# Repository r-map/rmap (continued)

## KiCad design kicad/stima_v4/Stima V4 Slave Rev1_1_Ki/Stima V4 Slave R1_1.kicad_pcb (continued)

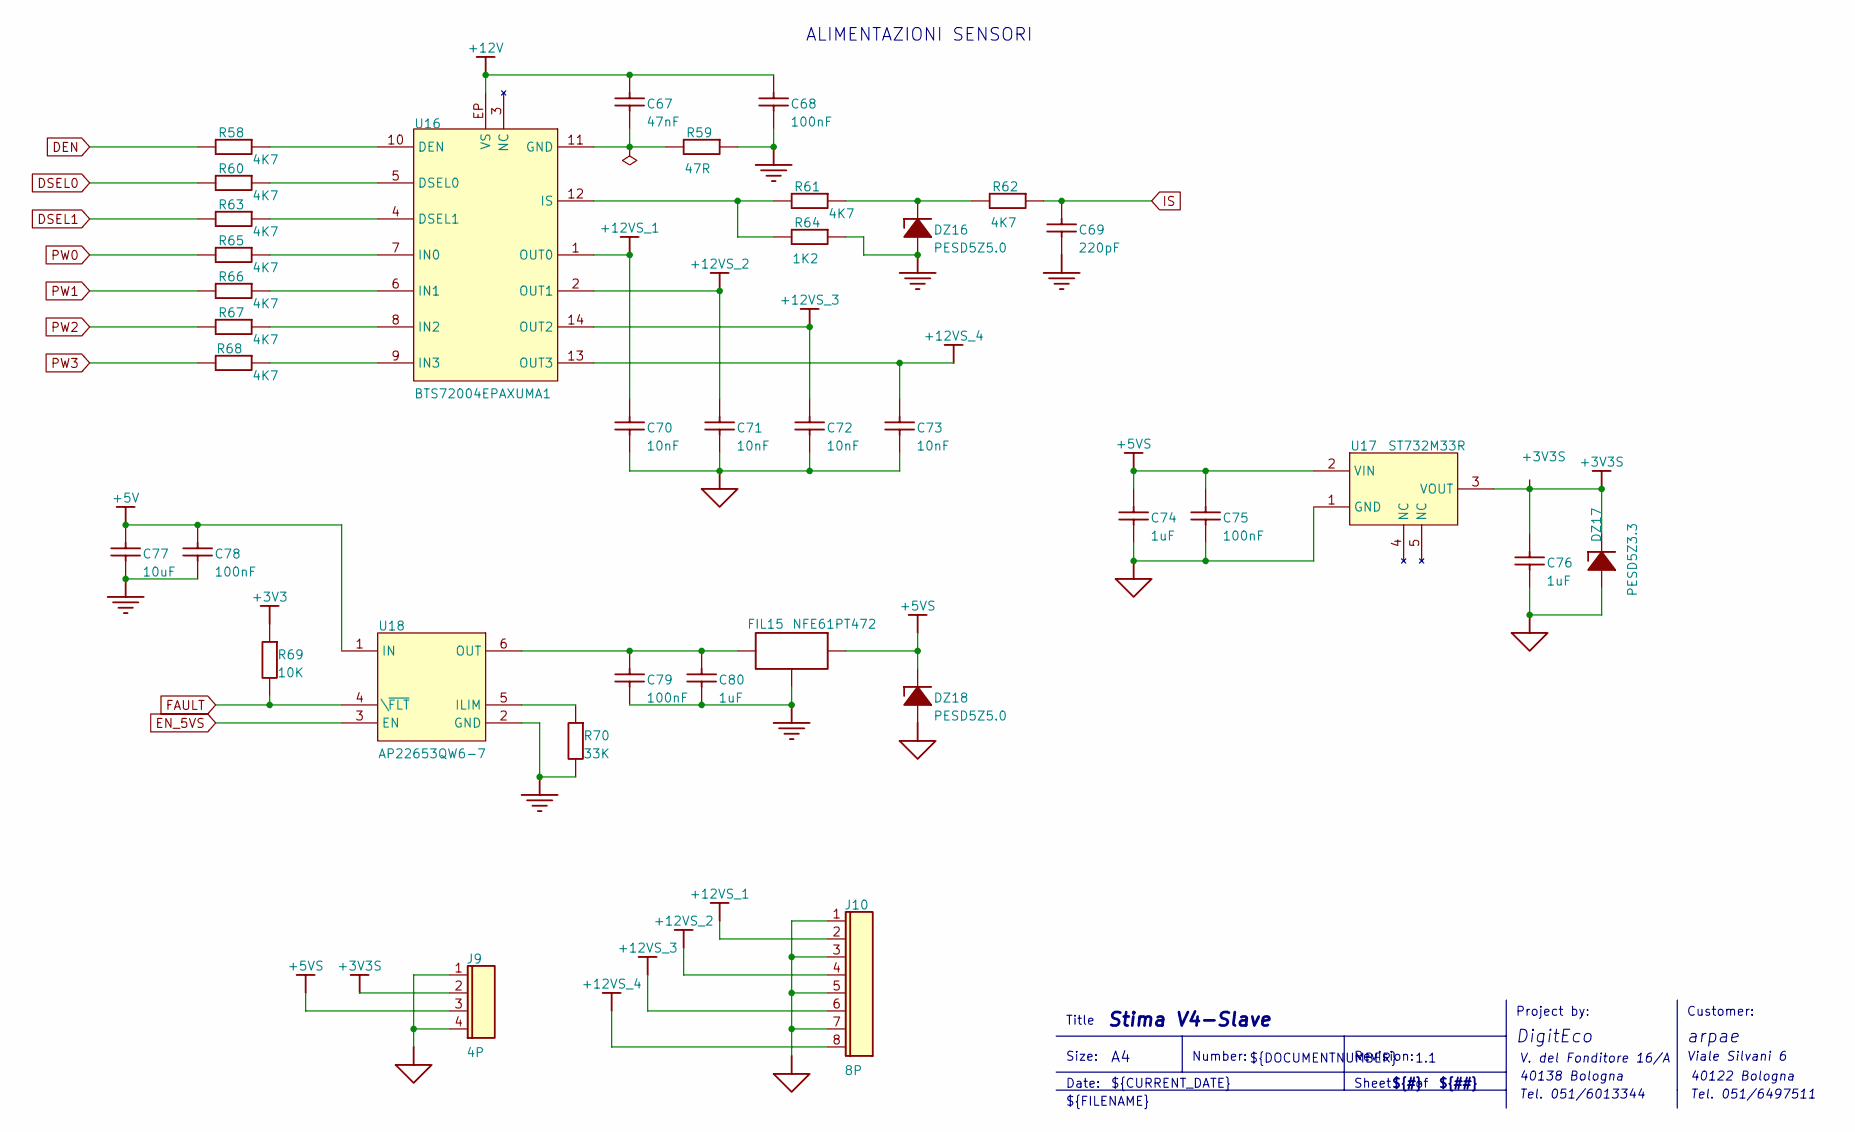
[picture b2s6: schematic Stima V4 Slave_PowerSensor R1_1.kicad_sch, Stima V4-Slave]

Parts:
+3V3S: TestPoint; TP
C67: 47nF; 0603; VOLTAGE 50V
C68, C75, C78, C79: 100nF; 0603; VOLTAGE 50V
C69: 220pF; 0603; VOLTAGE 50V
C70, C71, C72, C73: 10nF; 0603; VOLTAGE 50V
C74, C76, C80: 1uF; 0603; VOLTAGE 20V
C77: 10uF; 0603; VOLTAGE 20V
DZ16, DZ18: PESD5Z5.0; SOD 523(SC-79)
DZ17: PESD5Z3.3; SOD 523(SC-79)
FIL15: NFE61PT472; NFE61PT-2606
J9: 4P; CONN_4P-P381
J10: 8P; CONN_8P-P381
R58, R60, R61, R62, R63, R65, R66, R67, R68: 4K7; 0603
R59: 47R; 0603
R64: 1K2; 0603
R69: 10K; 0603
R70: 33K; 0603
U16: BTS72004EPAXUMA1; TSDSO-14
U17: ST732M33R; SOT23_5
U18: AP22653QW6-7; SOT26

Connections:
+3V3: R69.1; also elsewhere on the board
+3V3S: C76.1, DZ17.1 (K), J9.2, U17.3 (VOUT); also elsewhere on the board
+5V: C77.1, C78.1, U18.1 (IN); also elsewhere on the board
+5VS: C74.1, C75.1, DZ18.1 (K), FIL15.2 (O), J9.3, U17.2 (VIN); also elsewhere on the board
+12V: C67.1, C68.1, U16.EP (VS); also elsewhere on the board
+12VS_1: C70.1, J10.2, U16.1 (OUT0)
+12VS_2: C71.1, J10.4, U16.2 (OUT1)
+12VS_3: C72.1, J10.6, U16.14 (OUT2)
+12VS_4: C73.1, J10.8, U16.13 (OUT3); also elsewhere on the board
DEN: R58.1; also elsewhere on the board
DSEL0: R60.1; also elsewhere on the board
DSEL1: R63.1; also elsewhere on the board
EGND: C70.2, C71.2, C72.2, C73.2, C74.2, C75.2, C76.2, DZ17.2 (A), DZ18.2 (A), J9.1, J9.4, J10.1, J10.3, J10.5, J10.7, U17.1 (GND); also elsewhere on the board
EN_5VS: U18.3 (EN); also elsewhere on the board
FAULT: R69.2, U18.4 (\~FLT); also elsewhere on the board
GND: C68.2, C69.2, C77.2, C78.2, C79.2, C80.2, DZ16.2 (A), FIL15.3, R59.2, R64.2, R70.2, U18.2 (GND); also elsewhere on the board
IS: C69.1, R62.2; also elsewhere on the board
unnamed: DZ16.1 (K), R61.2, R62.1
unnamed: C79.1, C80.1, FIL15.1 (I), U18.6 (OUT)
unnamed: R58.2, U16.10 (DEN)
unnamed: R60.2, U16.5 (DSEL0)
unnamed: R63.2, U16.4 (DSEL1)
unnamed: C67.2, R59.1, U16.11 (GND)
unnamed: R65.2, U16.7 (IN0)
unnamed: R66.2, U16.6 (IN1)
unnamed: R67.2, U16.8 (IN2)
unnamed: R68.2, U16.9 (IN3)
unnamed: R61.1, R64.1, U16.12 (IS)
unnamed: R70.1, U18.5 (ILIM)
PW0: R65.1; also elsewhere on the board
PW1: R66.1; also elsewhere on the board
PW2: R67.1; also elsewhere on the board
PW3: R68.1; also elsewhere on the board

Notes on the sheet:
V. del Fonditore 16/A
Tel. 051/6013344
Title
Viale Silvani 6
ALIMENTAZIONI SENSORI
Size:
DigitEco
${##}
Tel. 051/6497511
arpae
Date:
${TITLE}
${#}
Project by:
Number:
${DOCUMENTNUMBER}
40122 Bologna
40138 Bologna
Revision:
Sheet
1.1
${FILENAME}
${CURRENT_DATE}
Customer:

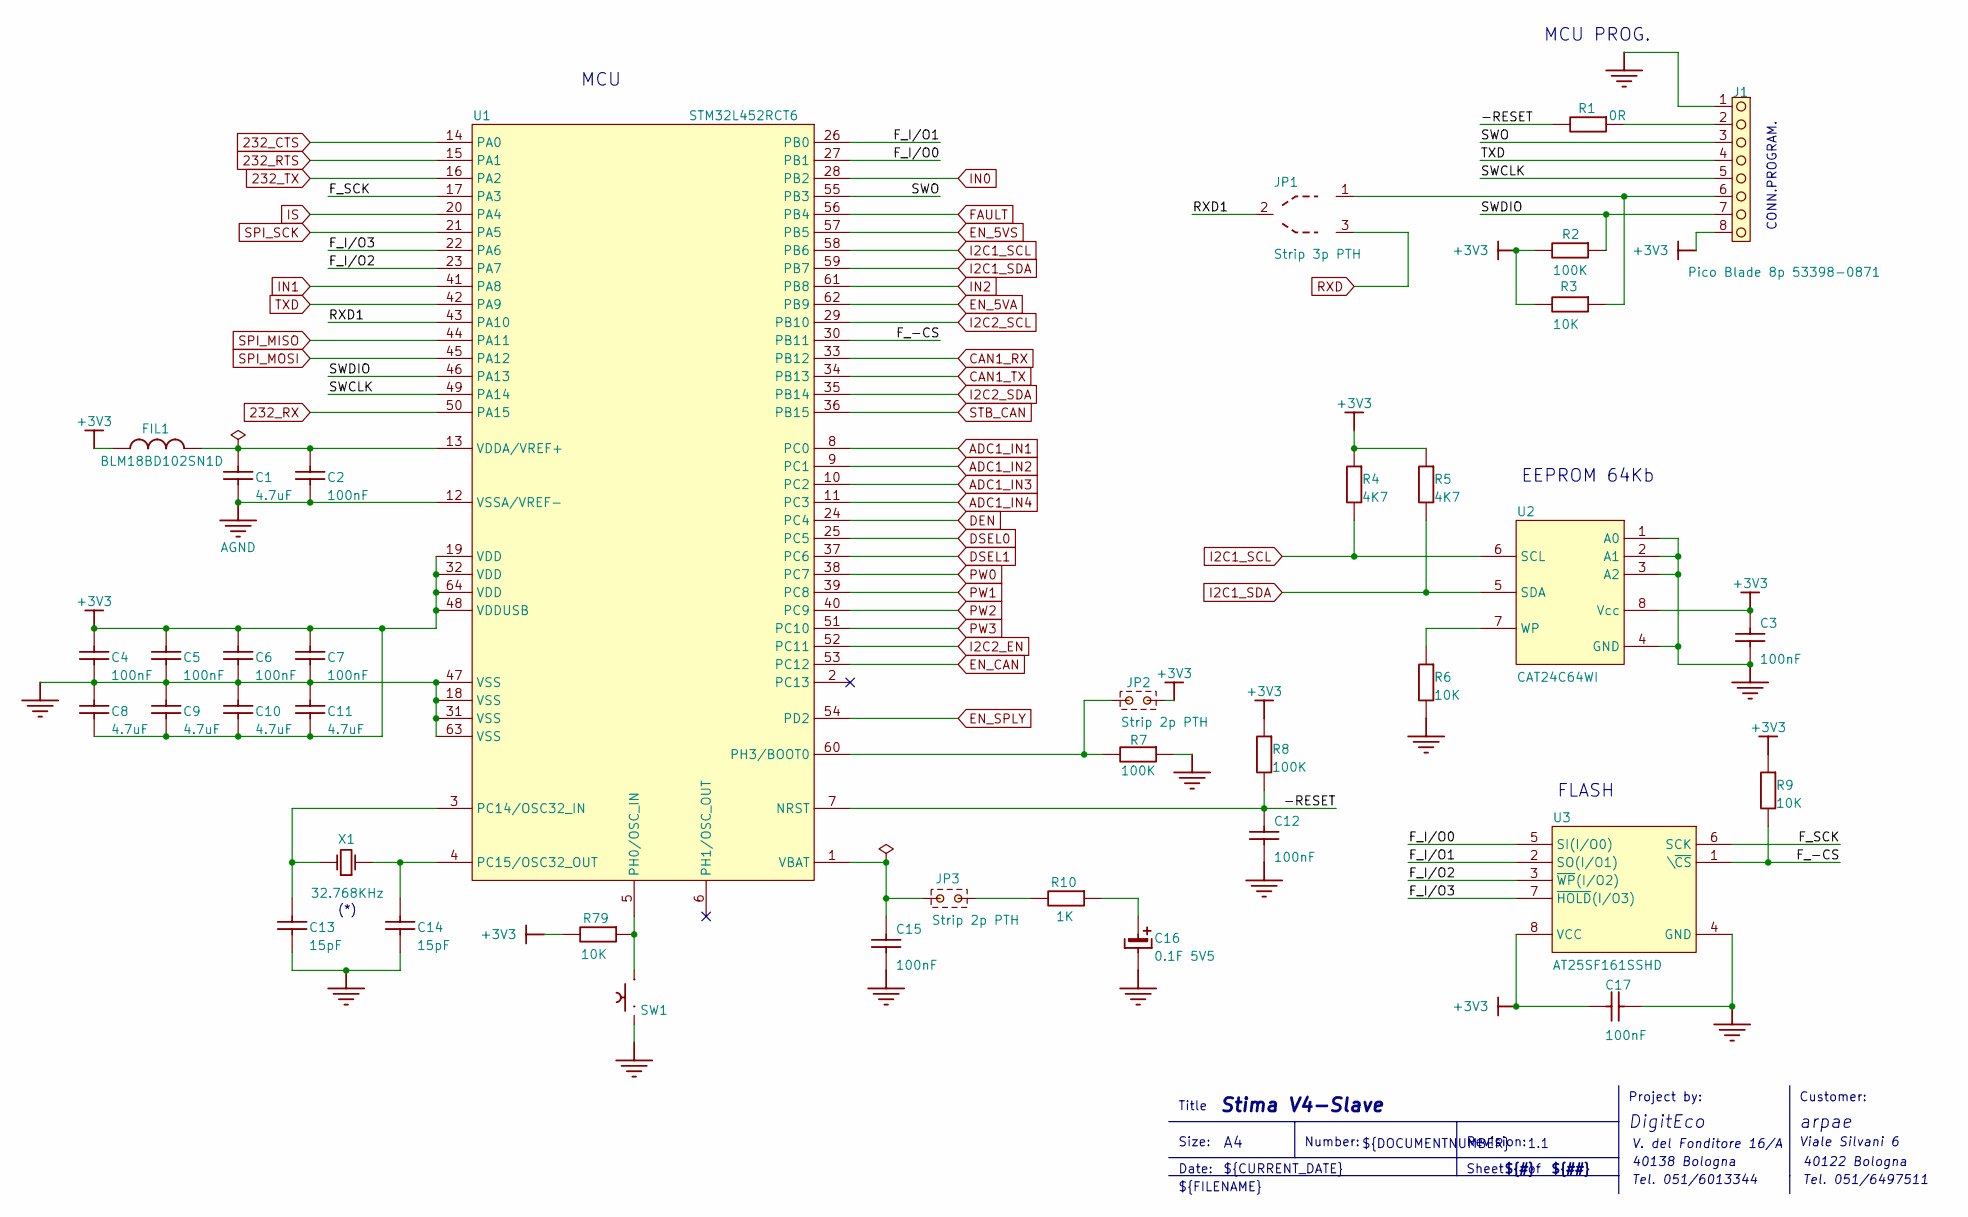
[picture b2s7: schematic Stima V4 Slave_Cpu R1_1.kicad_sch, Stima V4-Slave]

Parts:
C1, C8, C9, C10, C11: 4.7uF; 0603; VOLTAGE 16V
C2, C4, C5, C6, C7, C17: 100nF; 0603; VOLTAGE 50V
C3, C12, C15: 100nF; 0805; VOLTAGE 50V
C13, C14: 15pF; 0603; VOLTAGE 50V
C16: 0.1F 5V5; 10X8-10_5; VOLTAGE 5V5
FIL1: BLM18BD102SN1D; 0603
J1: Pico Blade 8p 53398-0871; MOLEX8P1_25SMD
JP1: Strip 3p PTH; STRIP3PP254
JP2, JP3: Strip 2p PTH; STRIP2P
R1: 0R; 0603
R2, R7, R8: 100K; 0603
R3, R6, R9, R79: 10K; 0603
R4, R5: 4K7; 0603
R10: 1K; 0603
SW1: B3F xx; TASTO SMD 6X6
U1: STM32L452RCT6; LQFP64
U2: CAT24C64WI; SO8
U3: AT25SF161SSHD; SO8
X1: 32.768KHz; CRYST_ECS

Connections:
232_CTS: U1.14 (PA0); also elsewhere on the board
232_RTS: U1.15 (PA1); also elsewhere on the board
232_RX: U1.50 (PA15); also elsewhere on the board
232_TX: U1.16 (PA2); also elsewhere on the board
+3V3: C3.1, C4.1, C5.1, C6.1, C7.1, C8.2, C9.2, C10.2, C11.2, C17.1, FIL1.1, J1.8, JP2.2, R2.1, R3.1, R4.2, R5.2, R8.2, R9.2, R79.2, U1.19 (VDD), U1.32 (VDD), U1.48 (VDDUSB), U1.64 (VDD), U2.8 (Vcc), U3.8 (VCC); also elsewhere on the board
/Stima V4 Slave_Cpu R1_1/-RESET: C12.1, R1.1, R8.1, U1.7 (NRST)
/Stima V4 Slave_Cpu R1_1/F_-CS: R9.1, U1.30 (PB11), U3.1 (\~CS)
/Stima V4 Slave_Cpu R1_1/F_I/O0: U1.27 (PB1), U3.5 (SI(I/O0))
/Stima V4 Slave_Cpu R1_1/F_I/O1: U1.26 (PB0), U3.2 (SO(I/O1))
/Stima V4 Slave_Cpu R1_1/F_I/O2: U1.23 (PA7), U3.3 (~WP(I/O2))
/Stima V4 Slave_Cpu R1_1/F_I/O3: U1.22 (PA6), U3.7 (~HOLD(I/O3))
/Stima V4 Slave_Cpu R1_1/F_SCK: U1.17 (PA3), U3.6 (SCK)
/Stima V4 Slave_Cpu R1_1/RXD1: JP1.2, U1.43 (PA10)
/Stima V4 Slave_Cpu R1_1/SWCLK: J1.5, U1.49 (PA14)
/Stima V4 Slave_Cpu R1_1/SWDIO: J1.7, R2.2, U1.46 (PA13)
/Stima V4 Slave_Cpu R1_1/SWO: J1.3, U1.55 (PB3)
ADC1_IN1: U1.8 (PC0); also elsewhere on the board
ADC1_IN2: U1.9 (PC1); also elsewhere on the board
ADC1_IN3: U1.10 (PC2); also elsewhere on the board
ADC1_IN4: U1.11 (PC3); also elsewhere on the board
AGND: C1.2, C2.2, U1.12 (VSSA/VREF-); also elsewhere on the board
CAN1_RX: U1.33 (PB12); also elsewhere on the board
CAN1_TX: U1.34 (PB13); also elsewhere on the board
DEN: U1.24 (PC4); also elsewhere on the board
DSEL0: U1.25 (PC5); also elsewhere on the board
DSEL1: U1.37 (PC6); also elsewhere on the board
EN_5VA: U1.62 (PB9); also elsewhere on the board
EN_5VS: U1.57 (PB5); also elsewhere on the board
EN_CAN: U1.53 (PC12); also elsewhere on the board
EN_SPLY: U1.54 (PD2); also elsewhere on the board
FAULT: U1.56 (PB4); also elsewhere on the board
GND: C3.2, C4.2, C5.2, C6.2, C7.2, C8.1, C9.1, C10.1, C11.1, C12.2, C13.2, C14.2, C15.2, C16.2, C17.2, J1.1, R6.1, R7.2, SW1.1, SW1.2, U1.18 (VSS), U1.31 (VSS), U1.47 (VSS), U1.63 (VSS), U2.1 (A0), U2.2 (A1), U2.3 (A2), U2.4 (GND), U3.4 (GND); also elsewhere on the board
I2C1_SCL: R4.1, U1.58 (PB6), U2.6 (SCL); also elsewhere on the board
I2C1_SDA: R5.1, U1.59 (PB7), U2.5 (SDA); also elsewhere on the board
I2C2_EN: U1.52 (PC11); also elsewhere on the board
I2C2_SCL: U1.29 (PB10); also elsewhere on the board
I2C2_SDA: U1.35 (PB14); also elsewhere on the board
IN0: U1.28 (PB2); also elsewhere on the board
IN1: U1.41 (PA8); also elsewhere on the board
IN2: U1.61 (PB8); also elsewhere on the board
IS: U1.20 (PA4); also elsewhere on the board
unnamed: C16.1, R10.2
unnamed: J1.2, R1.2
unnamed: J1.6, JP1.1, R3.2
unnamed: JP3.2, R10.1
unnamed: C13.1, U1.3 (PC14/OSC32_IN), X1.2 (OSC2)
unnamed: C14.1, U1.4 (PC15/OSC32_OUT), X1.1 (OSC1)
unnamed: R79.1, SW1.3, SW1.4, U1.5 (PH0/OSC_IN)
unnamed: JP2.1, R7.1, U1.60 (PH3/BOOT0)
unnamed: C15.1, JP3.1, U1.1 (VBAT)
unnamed: C1.1, C2.1, FIL1.2, U1.13 (VDDA/VREF+)
unnamed: R6.2, U2.7 (WP)
PW0: U1.38 (PC7); also elsewhere on the board
PW1: U1.39 (PC8); also elsewhere on the board
PW2: U1.40 (PC9); also elsewhere on the board
PW3: U1.51 (PC10); also elsewhere on the board
RXD: JP1.3; also elsewhere on the board
SPI_MISO: U1.44 (PA11); also elsewhere on the board
SPI_MOSI: U1.45 (PA12); also elsewhere on the board
SPI_SCK: U1.21 (PA5); also elsewhere on the board
STB_CAN: U1.36 (PB15); also elsewhere on the board
TXD: J1.4, U1.42 (PA9); also elsewhere on the board

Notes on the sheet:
MCU
(*)
${FILENAME}
1.1
${##}
Viale Silvani 6
Project by:
${DOCUMENTNUMBER}
Title
EEPROM 64Kb
Tel. 051/6013344
${CURRENT_DATE}
Date:
${TITLE}
Number:
40122 Bologna
arpae
MCU PROG.
Customer:
Revision:
DigitEco
Sheet
V. del Fonditore 16/A
Size:
Tel. 051/6497511
40138 Bologna
${#}
CONN.PROGRAM.
FLASH

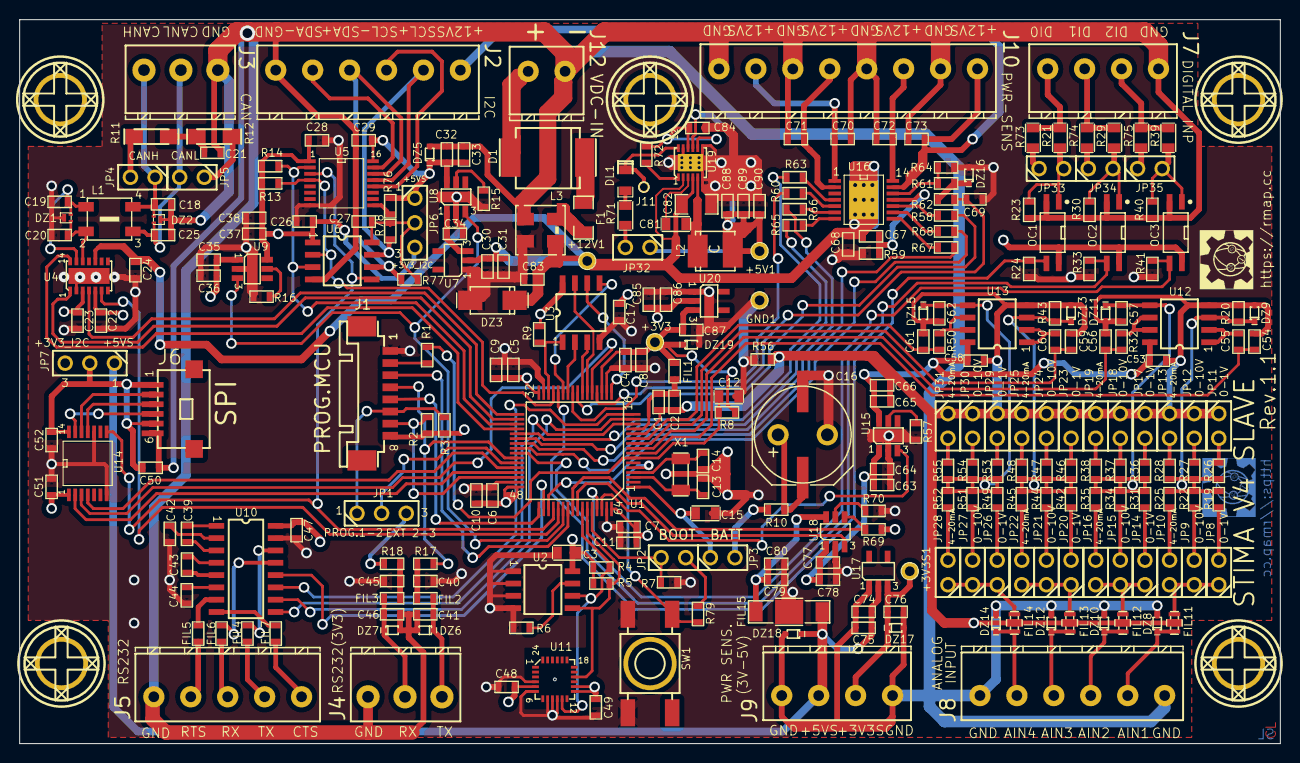
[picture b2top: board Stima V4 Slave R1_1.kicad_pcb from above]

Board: 4 copper layers, 130.0 x 74.7 mm, 288 parts (1 on the bottom side), 184 nets.

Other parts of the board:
+3V3S1: TestPoint; TP

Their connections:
+3V3S: +3V3S1.1; also elsewhere on the board

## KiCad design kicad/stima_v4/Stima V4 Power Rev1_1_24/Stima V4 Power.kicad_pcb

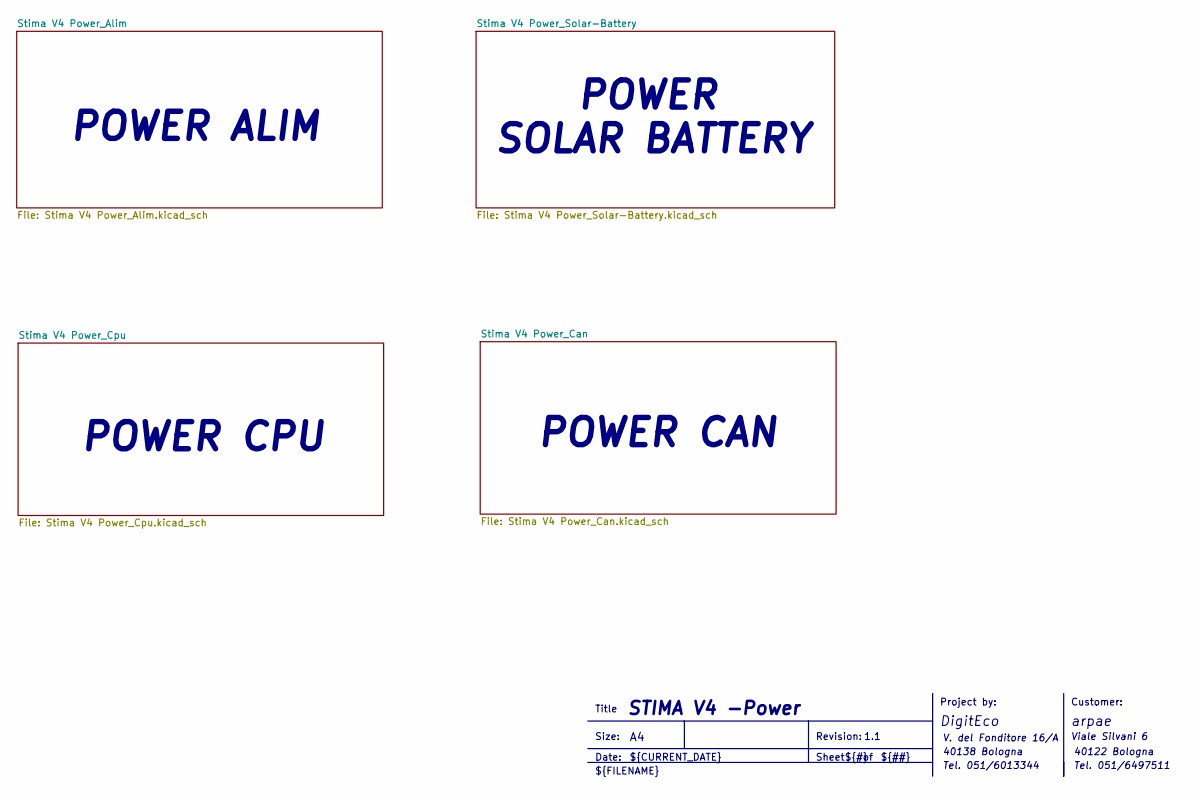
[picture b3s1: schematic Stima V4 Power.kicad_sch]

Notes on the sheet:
Tel. 051/6013344
${#}
arpae
POWER ALIM
Revision:
40138 Bologna
${TITLE}
Size:
V. del Fonditore 16/A
${##}
Viale Silvani 6
${CURRENT_DATE}
Sheet
Tel. 051/6497511
Date:
POWER SOLAR BATTERY
Customer:
40122 Bologna
Project by:
${FILENAME}
STIMA V4 -Power
DigitEco
Title
1.1
POWER CAN
POWER CPU

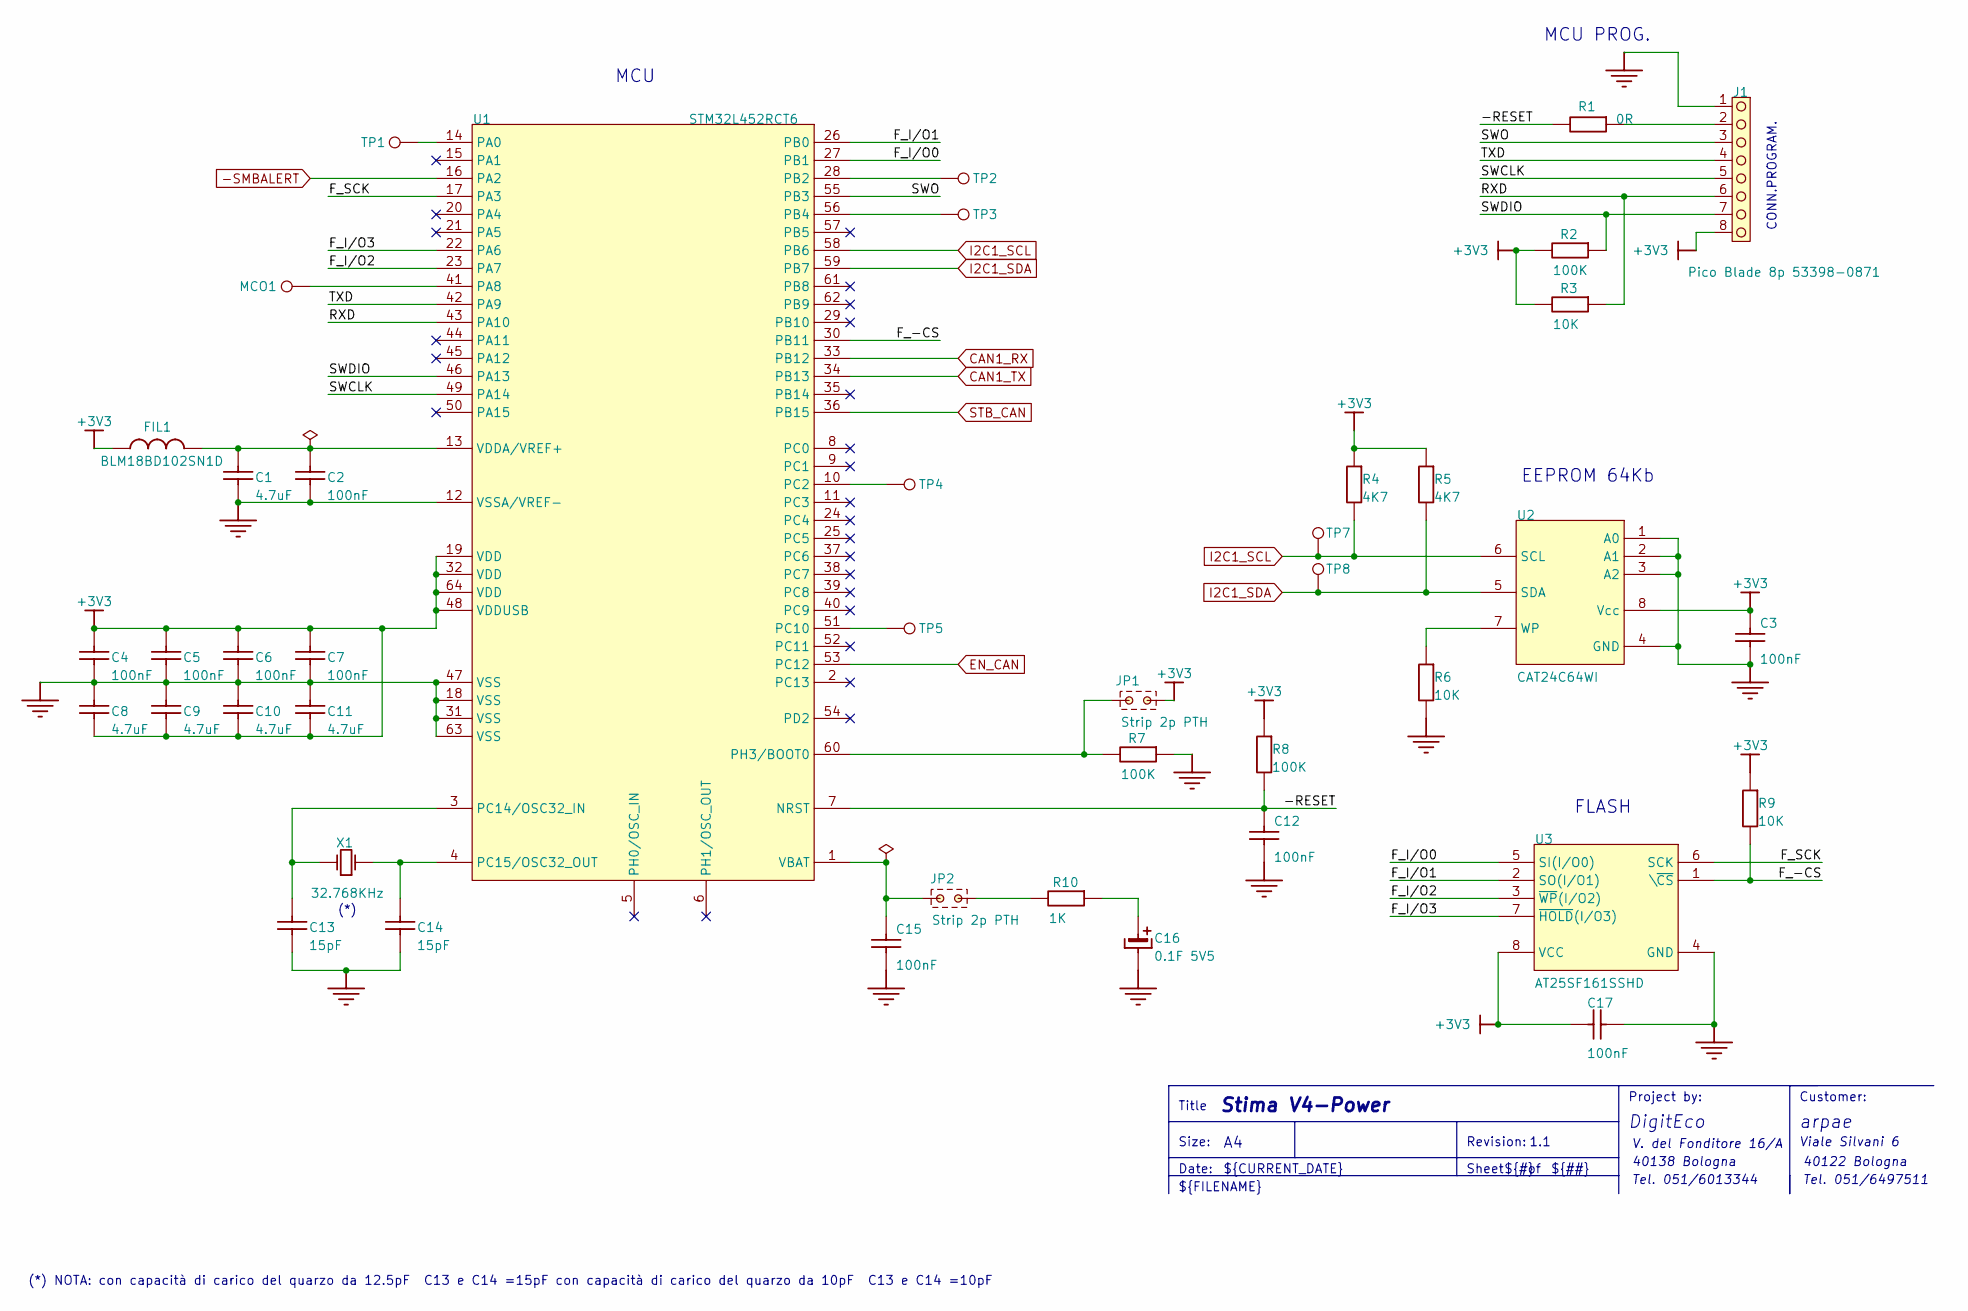
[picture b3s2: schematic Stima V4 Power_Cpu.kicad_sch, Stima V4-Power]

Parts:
C1, C8, C9, C10, C11: 4.7uF; 0603; VOLTAGE 16V
C2, C3, C4, C5, C6, C7, C12, C15, C17: 100nF; 0603; VOLTAGE 50V
C13, C14: 15pF; 0603; VOLTAGE 50V
C16: 0.1F 5V5; CapELSUPERCAP-3D FT0H104ZF; VOLTAGE 5V5
FIL1: BLM18BD102SN1D; 0603
J1: Pico Blade 8p 53398-0871; MOLEX8P1_25SMD
JP1, JP2: Strip 2p PTH; STRIP2P
MCO1: TestPoint; TP
R1: 0R; 0603
R2, R7, R8: 100K; 0603
R3, R6, R9: 10K; 0603
R4, R5: 4K7; 0603
R10: 1K; 0603
TP1, TP2, TP3, TP4, TP5, TP7, TP8: TestPoint; TP
U1: STM32L452RCT6; LQFP64
U2: CAT24C64WI; SO8
U3: AT25SF161SSHD; SO8
X1: 32.768KHz; CRYST_ECS

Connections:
+3V3: C3.1, C4.1, C5.1, C6.1, C7.1, C8.2, C9.2, C10.2, C11.2, C17.1, FIL1.1, J1.8, R2.1, R3.1, R4.2, R5.2, R8.2, R9.2, U1.19 (VDD), U1.32 (VDD), U1.48 (VDDUSB), U1.64 (VDD), U2.8 (Vcc), U3.8 (VCC); also elsewhere on the board
-SMBALERT: U1.16 (PA2); also elsewhere on the board
/Stima V4 Power_Cpu/-RESET: C12.1, R1.1, R8.1, U1.7 (NRST)
/Stima V4 Power_Cpu/F_-CS: R9.1, U1.30 (PB11), U3.1 (\~CS)
/Stima V4 Power_Cpu/F_I/O0: U1.27 (PB1), U3.5 (SI(I/O0))
/Stima V4 Power_Cpu/F_I/O1: U1.26 (PB0), U3.2 (SO(I/O1))
/Stima V4 Power_Cpu/F_I/O2: U1.23 (PA7), U3.3 (~WP(I/O2))
/Stima V4 Power_Cpu/F_I/O3: U1.22 (PA6), U3.7 (~HOLD(I/O3))
/Stima V4 Power_Cpu/F_SCK: U1.17 (PA3), U3.6 (SCK)
/Stima V4 Power_Cpu/RXD: J1.6, R3.2, U1.43 (PA10)
/Stima V4 Power_Cpu/SWCLK: J1.5, U1.49 (PA14)
/Stima V4 Power_Cpu/SWDIO: J1.7, R2.2, U1.46 (PA13)
/Stima V4 Power_Cpu/SWO: J1.3, U1.55 (PB3)
/Stima V4 Power_Cpu/TXD: J1.4, U1.42 (PA9)
CAN1_RX: U1.33 (PB12); also elsewhere on the board
CAN1_TX: U1.34 (PB13); also elsewhere on the board
EN_CAN: U1.53 (PC12); also elsewhere on the board
GND: C1.2, C2.2, C3.2, C4.2, C5.2, C6.2, C7.2, C8.1, C9.1, C10.1, C11.1, C12.2, C13.2, C14.2, C15.2, C16.2, C17.2, J1.1, R6.1, R7.2, U1.12 (VSSA/VREF-), U1.18 (VSS), U1.31 (VSS), U1.47 (VSS), U1.63 (VSS), U2.1 (A0), U2.2 (A1), U2.3 (A2), U2.4 (GND), U3.4 (GND); also elsewhere on the board
I2C1_SCL: R4.1, TP7.1, U1.58 (PB6), U2.6 (SCL); also elsewhere on the board
I2C1_SDA: R5.1, TP8.1, U1.59 (PB7), U2.5 (SDA); also elsewhere on the board
unnamed 25: R10.1; also elsewhere on the board
unnamed: C16.1, R10.2
unnamed: J1.2, R1.2
unnamed: TP1.1, U1.14 (PA0)
unnamed: MCO1.1, U1.41 (PA8)
unnamed: TP2.1, U1.28 (PB2)
unnamed: TP3.1, U1.56 (PB4)
unnamed: TP4.1, U1.10 (PC2)
unnamed: TP5.1, U1.51 (PC10)
unnamed: C13.1, U1.3 (PC14/OSC32_IN), X1.2 (OSC2)
unnamed: C14.1, U1.4 (PC15/OSC32_OUT), X1.1 (OSC1)
unnamed 59: R7.1, U1.60 (PH3/BOOT0); also elsewhere on the board
unnamed 60: C15.1, U1.1 (VBAT); also elsewhere on the board
unnamed: C1.1, C2.1, FIL1.2, U1.13 (VDDA/VREF+)
unnamed: R6.2, U2.7 (WP)
STB_CAN: U1.36 (PB15); also elsewhere on the board

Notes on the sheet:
${FILENAME}
MCU PROG.
EEPROM 64Kb
${##}
V. del Fonditore 16/A
Title
Revision:
Date:
MCU
40122 Bologna
Sheet
Tel. 051/6497511
Tel. 051/6013344
arpae
DigitEco
${#}
Viale Silvani 6
Customer:
(*) NOTA: con capacità di carico del quarzo da 12.5pF C13 e C14 =15pF con capacità di carico del quarzo da 10pF C13 e C14 =10pF
(*)
${TITLE}
1.1
${CURRENT_DATE}
CONN.PROGRAM.
Project by:
Size:
40138 Bologna
FLASH

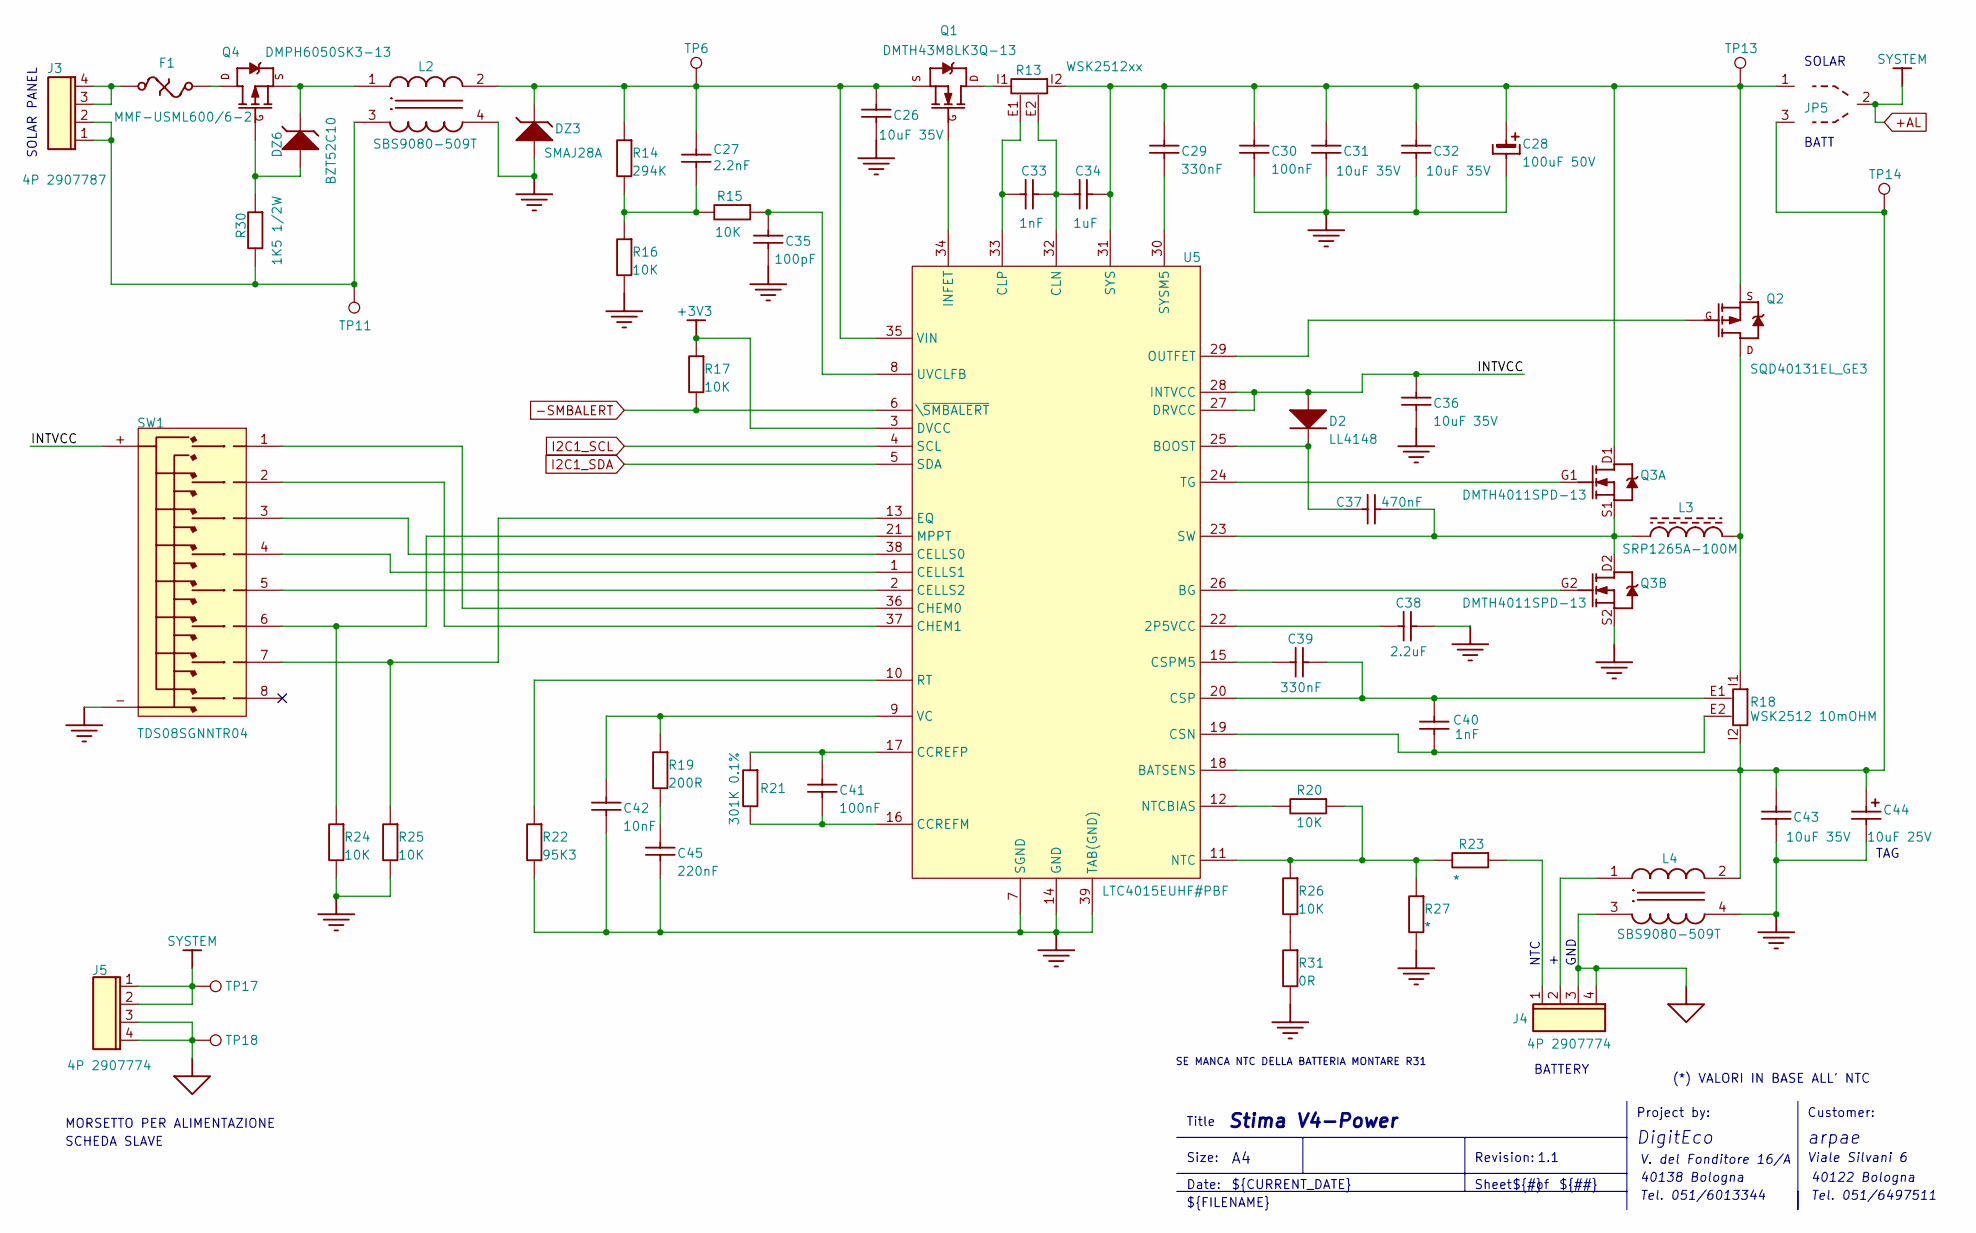
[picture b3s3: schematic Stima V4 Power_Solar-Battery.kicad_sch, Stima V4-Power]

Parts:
C26, C31, C32, C36, C43: 10uF 35V; 0603; VOLTAGE 35V
C27: 2.2nF; 0603; VOLTAGE 50V
C28: 100uF 50V; 8X10_5; VOLTAGE 50V
C29: 330nF; 0603; VOLTAGE 50V
C30, C41: 100nF; 0603; VOLTAGE 50V
C33, C40: 1nF; 0603; VOLTAGE 50V
C34: 1uF; 0603; VOLTAGE 50V
C35: 100pF; 0603; VOLTAGE 50V
C37: 470nF; 0603; VOLTAGE 50V
C38: 2.2uF; 0603; VOLTAGE 20V
C39: 330nF; 0805; VOLTAGE 50V
C42: 10nF; 0603; VOLTAGE 50V
C44: 10uF 25V; Case C-TC6032-2412; VOLTAGE 25V
C45: 220nF; 0603; VOLTAGE 50V
D2: LL4148; DSOD80
DZ3: SMAJ28A; SMA
DZ6: BZT52C10; SOD-123
F1: MMF-USML600/6-2; 1210
J3: 4P 2907787; CONN_4P-P508
J4, J5: 4P 2907774; CONN_4P-P508
JP5: JUMP3S
L2: SBS9080-509T; _Altium_ARGO_ARGO.PcbLib_FILTRO KEMET SBS9080
L3: SRP1265A-100M; COIL BOURNS SRP1265A-MIO
L4: SBS9080-509T; FILTRO KEMET SBS9080-MIO
Q1: DMTH43M8LK3Q-13; TO252 (DPAK)
Q2: SQD40131EL_GE3; TO252 (DPAK)
Q3: DMTH4011SPD-13; POWERDI5060-8-MIO
Q4: DMPH6050SK3-13; TO252 (DPAK)
R13: WSK2512xx; RES CURRSENS 4P WSK2512
R14: 294K; 0603
R15, R16, R17, R20, R24, R25, R26: 10K; 0603
R18: WSK2512 10mOHM; RES CURRSENS 4P WSK2512
R19: 200R; 0603
R21: 301K 0.1%; 0603
R22: 95K3; 0603
R23, R27: *; 0603
R30: 1K5 1/2W; 1206
R31: 0R; 0603
SW1: TDS08SGNNTR04; DIPSWITCH8P-TRISTATE
TP6, TP11, TP13, TP14, TP17, TP18: TestPoint; TP
U5: LTC4015EUHF#PBF; UHF QFN38 MIO

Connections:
+3V3: R17.1, U5.3 (DVCC); also elsewhere on the board
+AL: J5.1, J5.2, JP5.2, TP17.1; also elsewhere on the board
-SMBALERT: R17.2, U5.6 (\~SMBALERT); also elsewhere on the board
/Stima V4 Power_Solar-Battery/INTVCC: C36.1, D2.2 (A), SW1.+, U5.27 (DRVCC), U5.28 (INTVCC)
GND: C26.2, C28.2, C30.2, C31.2, C32.2, C35.2, C36.2, C38.2, C42.2, C43.2, C44.2, C45.2, DZ3.2 (A), L2.4, L4.4, Q3.S2, R16.1, R22.1, R24.1, R25.1, R27.2, R31.1, SW1.-, U5.7 (SGND), U5.14 (GND), U5.39 (TAB(GND)); also elsewhere on the board
I2C1_SCL: U5.4 (SCL); also elsewhere on the board
I2C1_SDA: U5.5 (SDA); also elsewhere on the board
unnamed: C27.2, R14.1, R15.1, R16.2
unnamed: C45.1, R19.1
unnamed: C37.1, D2.1 (K), U5.25 (BOOST)
unnamed: C26.1, C27.1, DZ3.1 (K), L2.2, Q1.3 (S), R14.2, TP6.1, U5.35 (VIN)
unnamed: DZ6.2 (A), Q4.1 (G), R30.2
unnamed: DZ6.1 (K), L2.1, Q4.3 (S)
unnamed: F1.1, J3.3, J3.4
unnamed: J3.1, J3.2, L2.3, R30.1, TP11.1
unnamed: Q1.2 (D), R13.I1
unnamed: Q1.1 (G), U5.34 (INFET)
unnamed: L3.2, Q2.2 (D), R18.I1
unnamed: Q2.1 (G), U5.29 (OUTFET)
unnamed: C28.1, C29.1, C30.1, C31.1, C32.1, C34.2, JP5.1, Q2.3 (S), Q3.D1, R13.I2, TP13.1, U5.31 (SYS)
unnamed: F1.2, Q4.2 (D)
unnamed: R26.1, R31.2
unnamed: C38.1, U5.22 (2P5VCC)
unnamed: C43.1, C44.1, JP5.3, L4.2, R18.I2, TP14.1, U5.18 (BATSENS)
unnamed: Q3.G2, U5.26 (BG)
unnamed: C41.2, R21.1, U5.16 (CCREFM)
unnamed: C41.1, R21.2, U5.17 (CCREFP)
unnamed: SW1.3, U5.38 (CELLS0)
unnamed: SW1.4, U5.1 (CELLS1)
unnamed: SW1.5, U5.2 (CELLS2)
unnamed: SW1.1, U5.36 (CHEM0)
unnamed: SW1.2, U5.37 (CHEM1)
unnamed: C33.2, C34.1, R13.E2, U5.32 (CLN)
unnamed: C33.1, R13.E1, U5.33 (CLP)
unnamed: C40.2, R18.E2, U5.19 (CSN)
unnamed: C39.2, C40.1, R18.E1, U5.20 (CSP)
unnamed: C39.1, U5.15 (CSPM5)
unnamed: R25.2, SW1.7, U5.13 (EQ)
unnamed: R24.2, SW1.6, U5.21 (MPPT)
unnamed: R20.1, R23.2, R26.2, R27.1, U5.11 (NTC)
unnamed: R20.2, U5.12 (NTCBIAS)
unnamed: R22.2, U5.10 (RT)
unnamed: C37.2, L3.1, Q3.D2, Q3.S1, U5.23 (SW)
unnamed: C29.2, U5.30 (SYSM5)
unnamed: Q3.G1, U5.24 (TG)
unnamed: C35.1, R15.2, U5.8 (UVCLFB)
unnamed: C42.1, R19.2, U5.9 (VC)

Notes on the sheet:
SOLAR
40138 Bologna
Size:
SCHEDA SLAVE
V. del Fonditore 16/A
Customer:
NTC
DigitEco
Date:
BATT
SE MANCA NTC DELLA BATTERIA MONTARE R31
Sheet
(*) VALORI IN BASE ALL' NTC
arpae
Project by:
MORSETTO PER ALIMENTAZIONE
Tel. 051/6497511
Title
SOLAR PANEL
${#}
40122 Bologna
${TITLE}
1.1
TAG
${FILENAME}
Revision:
BATTERY
${CURRENT_DATE}
${##}
Tel. 051/6013344
Viale Silvani 6
GND

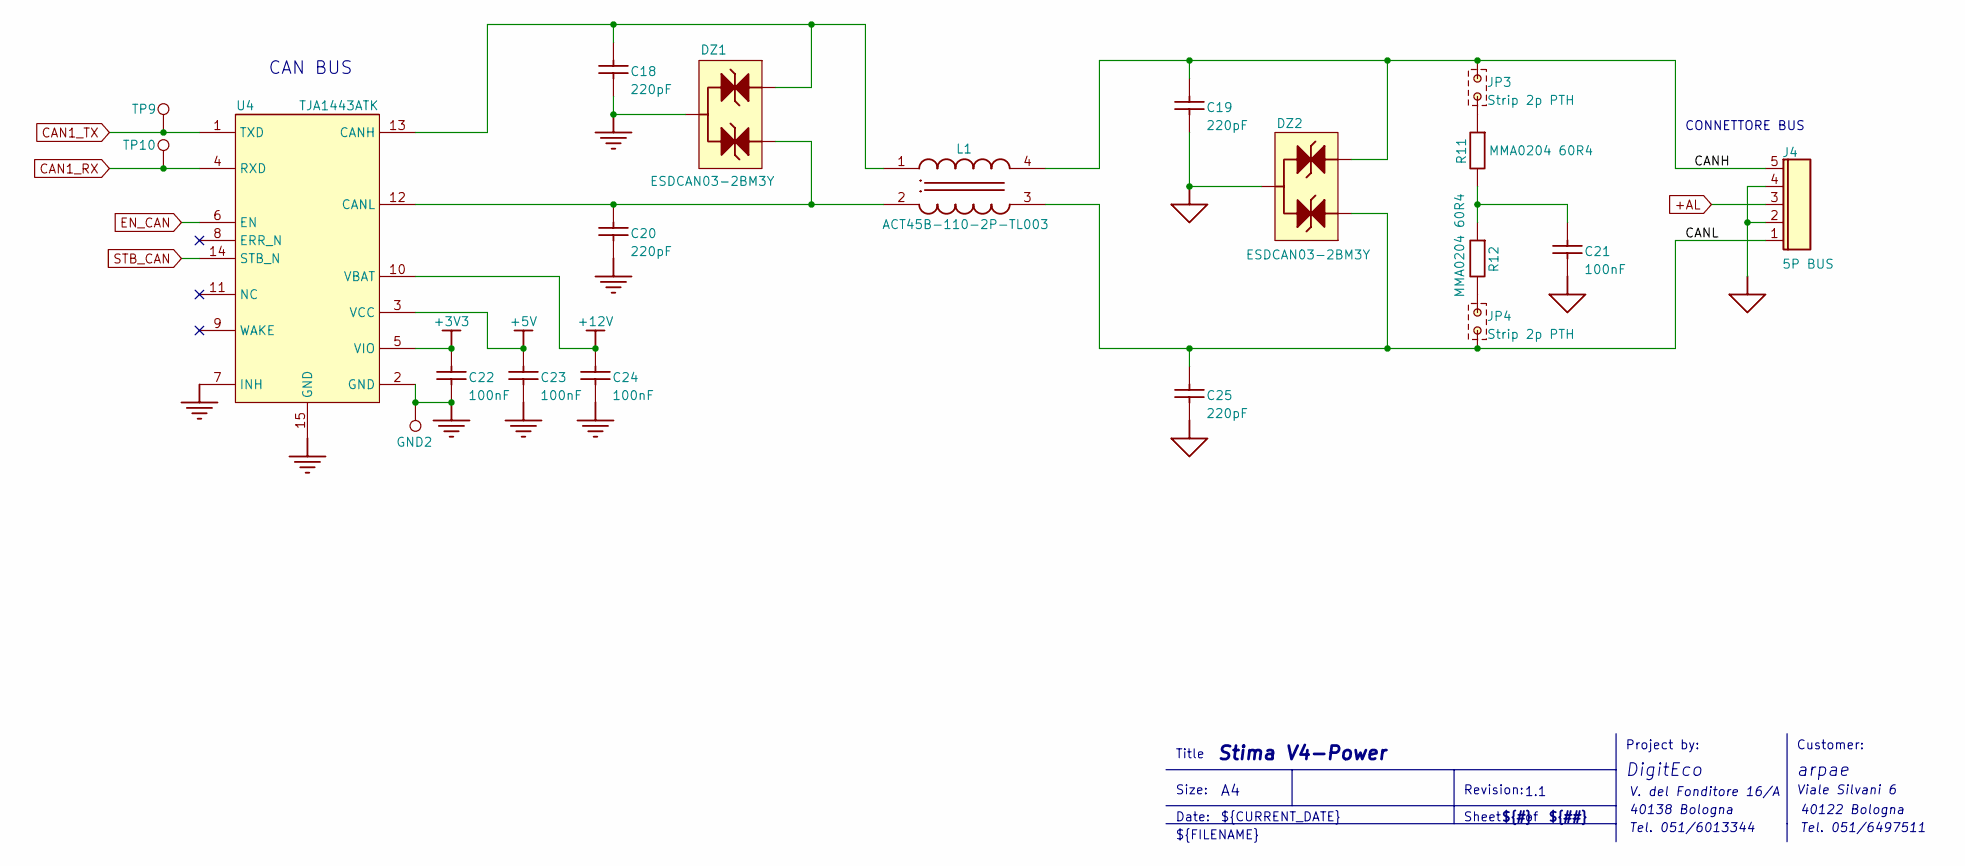
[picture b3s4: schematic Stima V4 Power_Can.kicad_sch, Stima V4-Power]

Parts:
C18, C19, C20, C25: 220pF; 0603; VOLTAGE 50V
C21, C22, C23, C24: 100nF; 0603; VOLTAGE 50V
DZ1, DZ2: ESDCAN03-2BM3Y; QFN-3L-DFN1110-MIO
GND2: TestPoint; TP
J4: 5P BUS; CONTATTI5
JP3, JP4: Strip 2p PTH; STRIP2P
L1: ACT45B-110-2P-TL003; ACT45B TDK-MIO
R11, R12: MMA0204 60R4; MELFRESMMA0204
TP9, TP10: TestPoint; TP
U4: TJA1443ATK; HVSON14 MIO

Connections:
+3V3: C22.1, U4.5 (VIO); also elsewhere on the board
+5V: C23.1, U4.3 (VCC); also elsewhere on the board
+12V: C24.2, U4.10 (VBAT); also elsewhere on the board
/Stima V4 Power_Can/CANH: C19.2, DZ2.1 (A/K), J4.5, JP3.1, L1.4; also elsewhere on the board
CAN1_RX: TP10.1, U4.4 (RXD); also elsewhere on the board
CAN1_TX: TP9.1, U4.1 (TXD); also elsewhere on the board
EN_CAN: U4.6 (EN); also elsewhere on the board
GND: C18.1, C20.1, C22.2, C23.2, C24.1, DZ1.3 (A/K), GND2.1, U4.2 (GND), U4.7 (INH), U4.15 (GND); also elsewhere on the board
unnamed: C21.2, R11.1, R12.2
unnamed: JP3.2, R11.2
unnamed: JP4.1, R12.1
unnamed: C18.2, DZ1.2 (A/K), L1.1, U4.13 (CANH)
unnamed: C20.2, DZ1.1 (A/K), L1.2, U4.12 (CANL)
STB_CAN: U4.14 (STB_N); also elsewhere on the board

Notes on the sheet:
Date:
V. del Fonditore 16/A
${#}
40138 Bologna
Viale Silvani 6
Project by:
Size:
Tel. 051/6497511
1.1
CAN BUS
arpae
${TITLE}
${CURRENT_DATE}
${##}
${FILENAME}
Title
Customer:
40122 Bologna
Tel. 051/6013344
CONNETTORE BUS
Sheet
DigitEco
Revision:
